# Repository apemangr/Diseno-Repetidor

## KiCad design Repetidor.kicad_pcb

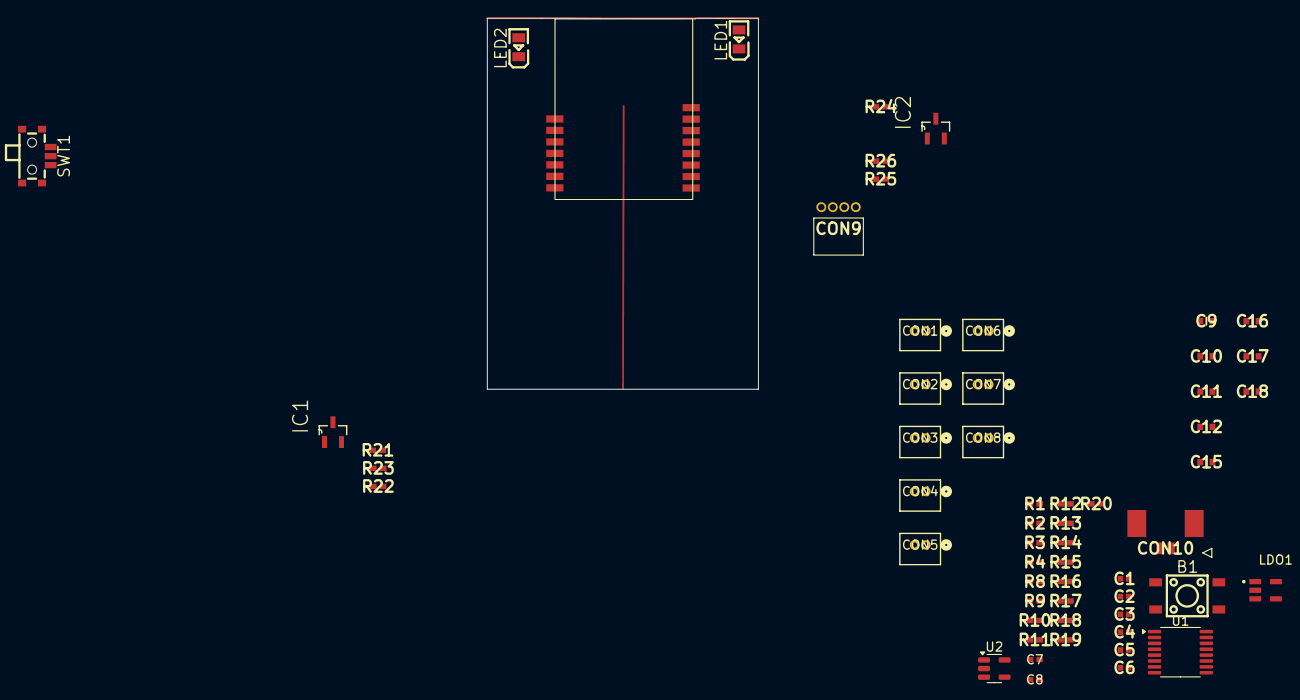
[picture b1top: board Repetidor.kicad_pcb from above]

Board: 2 copper layers, 30.0 x 41.0 mm, 59 parts (0 on the bottom side), 28 nets, no tracks yet.

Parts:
B1: SW_Push; K2-1109SP-G4SA-04
C1, C2, C3, C4: 1uf; CAPC1005X55N
C5, C6: 0.1uf; CAPC1005X55N
C7, C8: 4.7uf; CAP_GMC04_CCE
C9, C10, C11, C12, C15, C16, C17, C18: 47uf; GRM18x
CON1, CON2, CON3, CON4, CON5, CON6, CON7, CON8: Conn_01x02; CONN02_530470210_MOL
CON9: Conn_01x04; 8518700420001101
CON10: Conn_01x02; 533980271
HOLYIOT_1: Holyiot_YJ17029
IC1, IC2: IRLML6344TRPBF; SOT95P240X112-3N
LDO1: STLQ015M30R; SOT95P280X145-5N
LED1, LED2: LED; LED0805-R-RD
R1: 6.2M; RESC1005X40N
R2: 2.4M; RESC1005X40N
R3, R4, R11, R12, R13, R18, R19, R20: 6.2k; RESC1005X40N
R8, R14, R15, R16, R17, R23, R26: 10k; RESC1005X40N
R9, R22, R25: 1k; RESC1005X40N
R10: 0k; RESC1005X40N
R21, R24: 70; RESC1005X40N
SWT1: Conn_01x02; TA-3514-A1-B
U1: AD5593R; TSSOP-16_4.4x5mm_P0.65mm
U2: TLV70012_SOT23-5; SOT-23-5

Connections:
BAT+: C7.2, C8.2, C15.2, C16.2, C17.2, C18.2, CON10.1, R21.1, R24.1, SWT1.1
BOTON: C6.2, HOLYIOT_1.4 (P0.27), R8.2, R9.1
CIRCUITO_1: CON1.2, R3.2, U1.4 (IO0)
CIRCUITO_2: CON2.2, R4.2, U1.5 (IO1)
CIRCUITO_3: CON3.2, R11.2, U1.6 (IO2)
CIRCUITO_4: CON4.2, R12.2, U1.7 (IO3)
CIRCUITO_5: CON5.2, R13.2, U1.10 (IO4)
CIRCUITO_6: CON6.2, R18.2, U1.11 (IO5)
CIRCUITO_7: CON7.2, R19.2, U1.12 (IO6)
CIRCUITO_8: CON8.2, R20.2, U1.13 (IO7)
GND: B1.2, C1.1, C2.2, C3.2, C4.1, C5.2, C6.1, C7.1, C8.1, C9.1, C10.1, C11.1, C12.1, C15.1, C16.1, C17.1, C18.1, CON9.3, CON10.2, HOLYIOT_1.1 (GND), IC1.2 (S), IC2.2 (S), LDO1.2 (GND), R2.2, R3.1, R4.1, R11.1, R12.1, R13.1, R18.1, R19.1, R20.1, R23.1, R26.1, U1.14 (GND), U2.2 (GND)
LDO_MEDICION: C4.2, HOLYIOT_1.3 (P0.26), HOLYIOT_1.5 (P0.28), R14.1, R15.1, R16.1, R17.1, U1.3 (V_{DD}), U1.9 (V_{LOGIC}), U2.1 (IN), U2.3 (EN)
LED1: HOLYIOT_1.8 (P0.21), R22.1
LED2: HOLYIOT_1.9 (P0.18), R25.1
NIVEL_VOLTAJE: C5.1, R1.2, R2.1
unnamed: B1.1, R9.2
unnamed: IC1.1 (G), R22.2, R23.2
unnamed: IC2.3 (D), LED1.1 (K)
unnamed: IC2.1 (G), R25.2, R26.2
unnamed: LED1.2 (A), R24.2
unnamed: R15.2, U1.2 (A0)
unnamed: R16.2, U1.16 (SCL)
unnamed: R17.2, U1.15 (SDA)
unnamed: R14.2, U1.1 (~RESET)
SWDCLK: CON9.2, HOLYIOT_1.11 (SWDCLK)
V1.2: C3.1, CON1.1, CON2.1, CON3.1, CON4.1, CON5.1, CON6.1, CON7.1, CON8.1, U1.8 (V_{REF}), U2.5 (OUT)
V3: C2.1, C9.2, C10.2, C11.2, C12.2, CON9.4, HOLYIOT_1.2 (VDD), LDO1.5 (OUT), R8.1, R10.2
VIN: C1.2, LDO1.1 (IN), LDO1.3 (EN), R1.1, R10.1, SWT1.2

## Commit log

2025-05-14 Componentes con symbol y footprint listos, falta ubicarlos y agregar el modelo 3D
2025-05-14 Symbols y Footprints listos, falta acomodarlos y agregar 3D models
2025-11-03 Save for safety
